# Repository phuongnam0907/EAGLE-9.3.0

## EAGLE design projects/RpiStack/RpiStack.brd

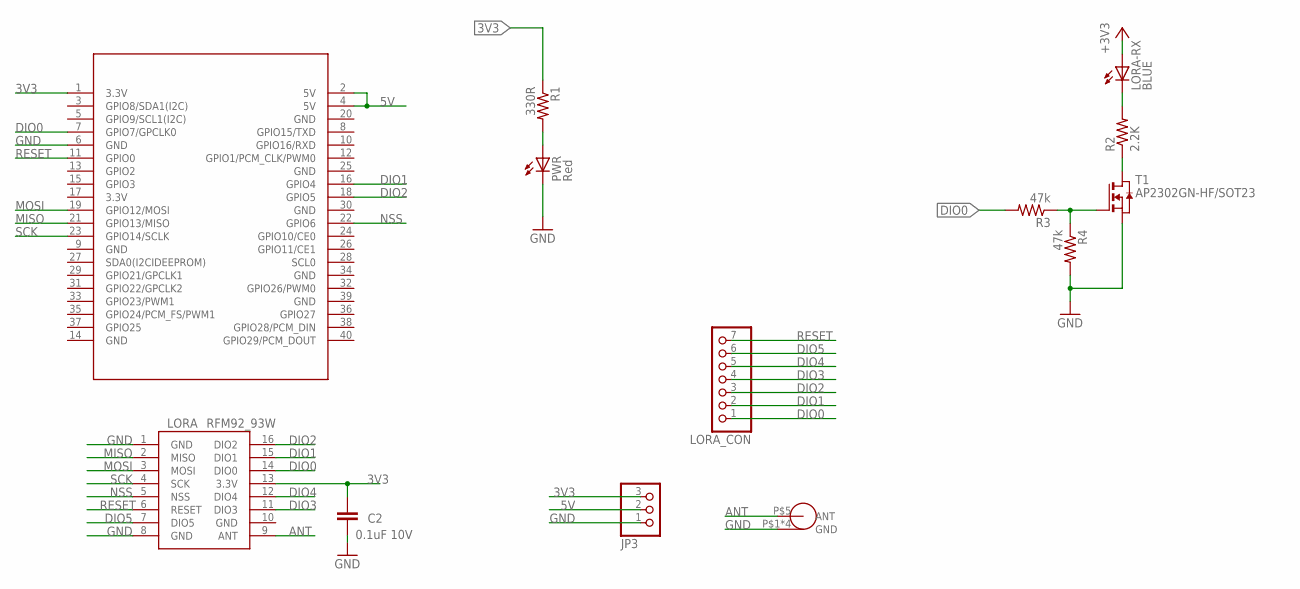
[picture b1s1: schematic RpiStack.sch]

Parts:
C2: 0.1uF 10V; C0402
JP3: PINHD-1X3; 1X03
LORA: RFM92_93W
LORA-RX: BLUE; CHIPLED_0603
LORA_ANT: SMA-KE
LORA_CON: PINHD-1X7; 1X07
PWR: Red; CHIPLED_0603
R1: 330R; R0402
R2: 2.2K; R0402
R3, R4: 47k; R0402
T1: AP2302GN-HF/SOT23; SOT-23
U$2: RPILORASHIELD

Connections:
3V3: C2.2, JP3.3, LORA.13 (3.3V), LORA-RX.A, R1.1, U$2.1 (3.3V)
5V: JP3.2, U$2.2 (5V), U$2.4 (5V)
/RESET: R2.1, T1.1 (D)
ANT: LORA.9 (ANT), LORA_ANT.P$5 (ANT)
DIO0: LORA.14 (DIO0), LORA_CON.1, R3.2, U$2.7 (GPIO7/GPCLK0)
DIO1: LORA.15 (DIO1), LORA_CON.2, U$2.16 (GPIO4)
DIO2: LORA.16 (DIO2), LORA_CON.3, U$2.18 (GPIO5)
DIO3: LORA.11 (DIO3), LORA_CON.4
DIO4: LORA.12 (DIO4), LORA_CON.5
DIO5: LORA.7 (DIO5), LORA_CON.6
GND: C2.1, JP3.1, LORA.1 (GND), LORA.8 (GND), LORA.10 (GND), LORA_ANT.P$1 (GND), LORA_ANT.P$2 (GND), LORA_ANT.P$3 (GND), LORA_ANT.P$4 (GND), PWR.C, R4.2, T1.2 (S), U$2.6 (GND)
MISO: LORA.2 (MISO), U$2.21 (GPIO13/MISO)
MOSI: LORA.3 (MOSI), U$2.19 (GPIO12/MOSI)
unnamed: R3.1, R4.1, T1.3 (G)
unnamed: PWR.A, R1.2
unnamed: LORA-RX.C, R2.2
NSS: LORA.5 (NSS), U$2.22 (GPIO6)
RESET: LORA.6 (RESET), LORA_CON.7, U$2.11 (GPIO0)
SCK: LORA.4 (SCK), U$2.23 (GPIO14/SCLK)

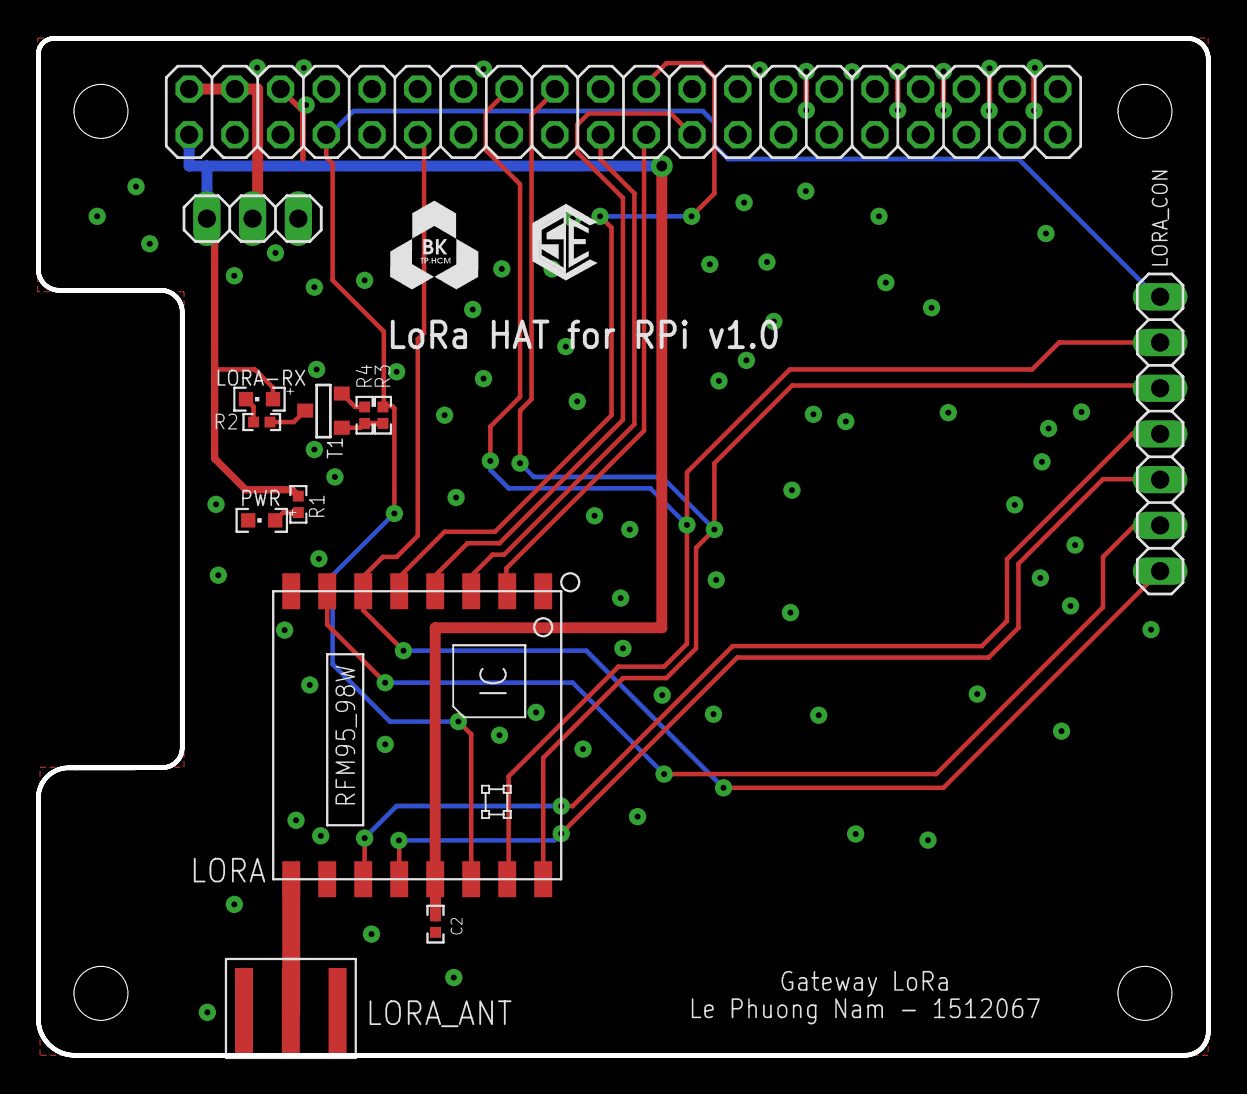
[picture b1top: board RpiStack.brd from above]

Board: 2 copper layers, 65.0 x 56.5 mm, 13 parts (0 on the bottom side), 19 nets.

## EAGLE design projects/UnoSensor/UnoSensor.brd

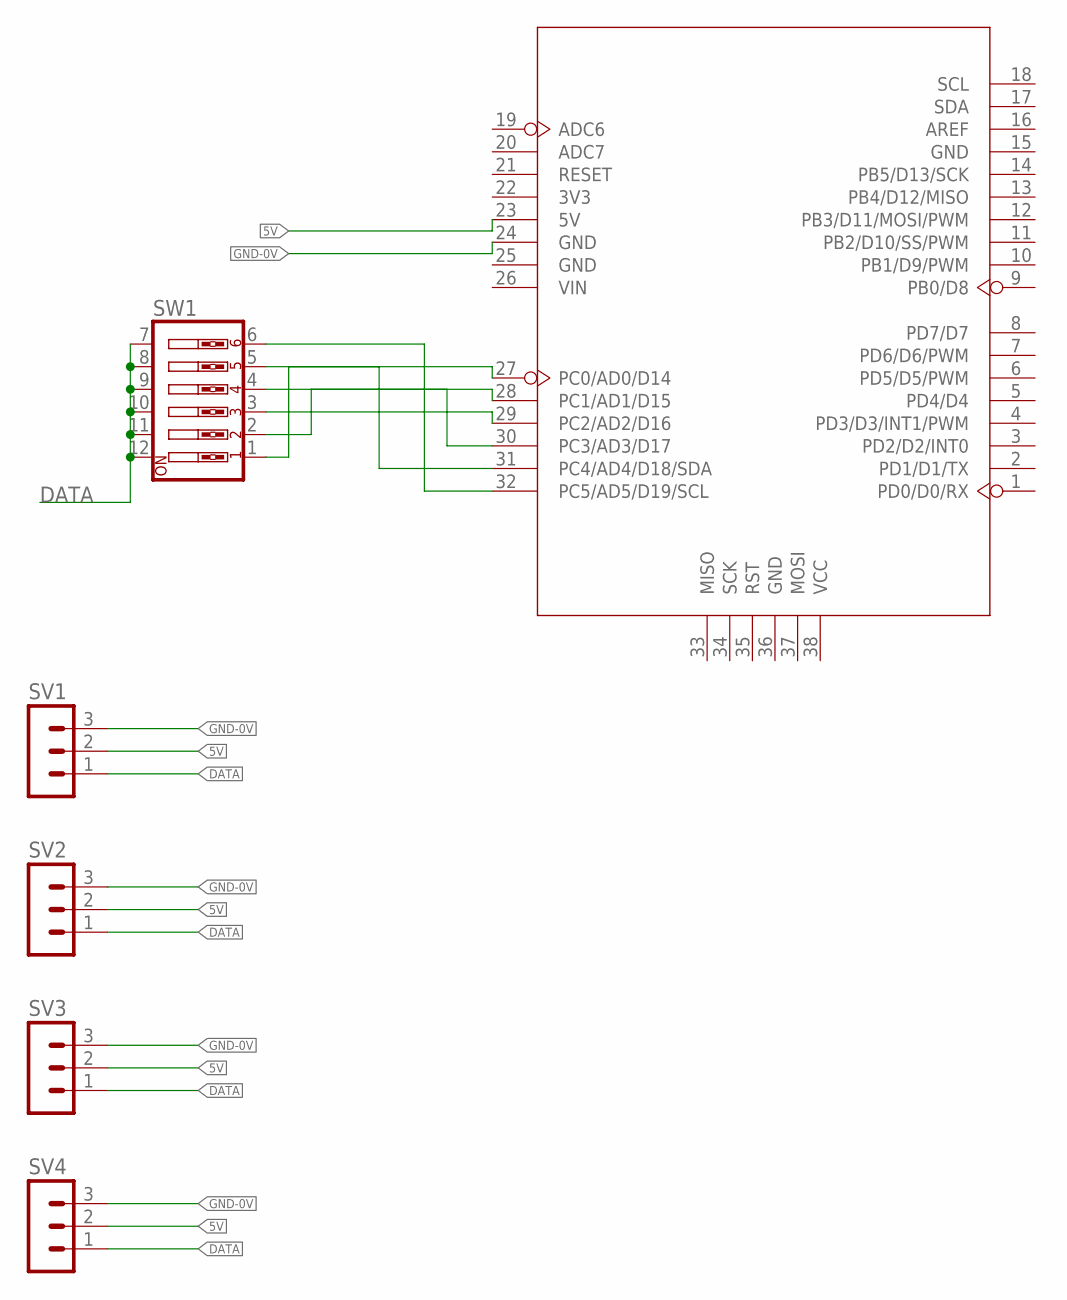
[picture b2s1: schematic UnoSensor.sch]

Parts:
SV1: 2; MA03-1
SV2, SV3, SV4: MA03-1
SW1: SW_DIP-6; EDG-06
U5: MOUDLE_ARDUINO-38P328P_NO_VIA; MOUDLE_ARDUINO-328P--

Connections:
5V: SV1.2, SV2.2, SV3.2, SV4.2, U5.23 (5V)
DATA: SV1.1, SV2.1, SV3.1, SV4.1, SW1.7, SW1.8, SW1.9, SW1.10, SW1.11, SW1.12
GND-0V: SV1.3, SV2.3, SV3.3, SV4.3, U5.24 (GND)
unnamed: SW1.1, U5.27 (PC0/AD0/D14)
unnamed: SW1.2, U5.28 (PC1/AD1/D15)
unnamed: SW1.3, U5.29 (PC2/AD2/D16)
unnamed: SW1.4, U5.30 (PC3/AD3/D17)
unnamed: SW1.5, U5.31 (PC4/AD4/D18/SDA)
unnamed: SW1.6, U5.32 (PC5/AD5/D19/SCL)

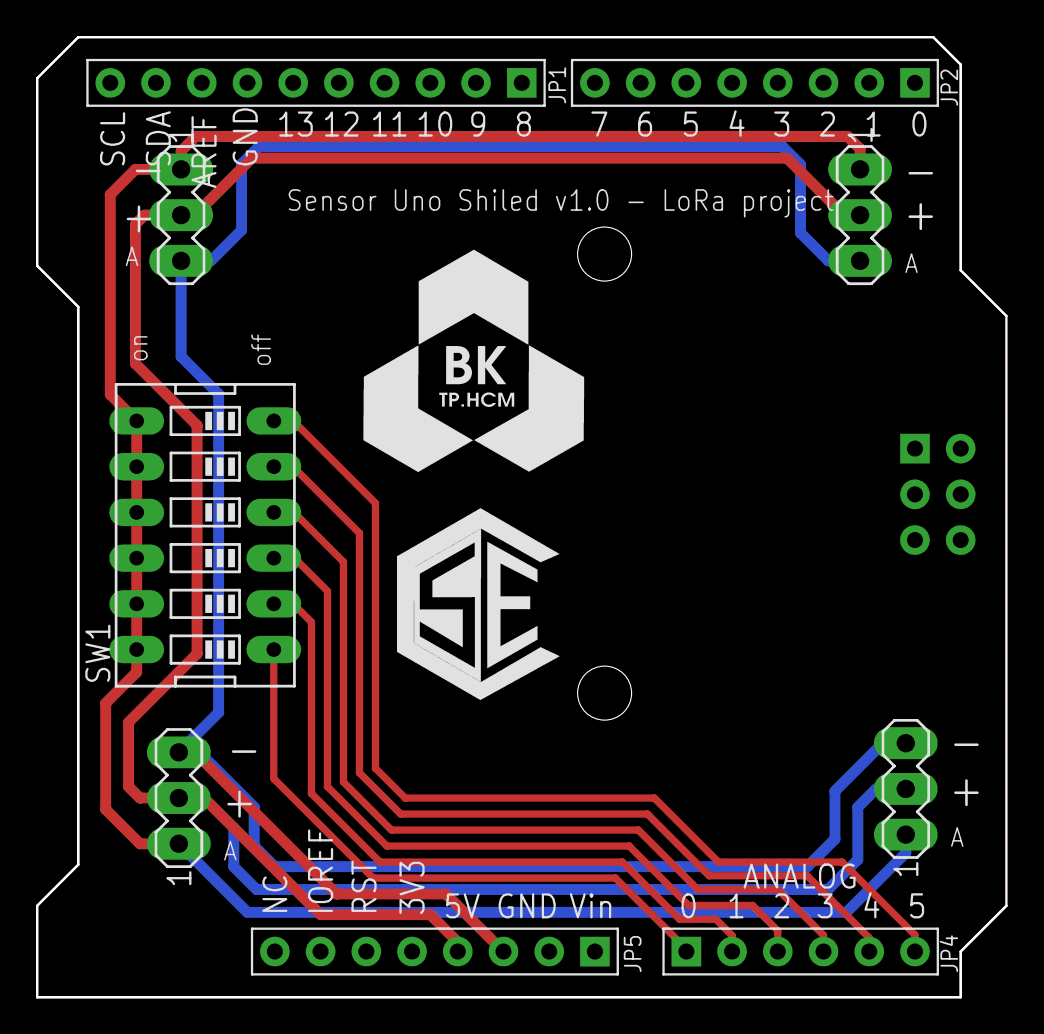
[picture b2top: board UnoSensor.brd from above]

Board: 2 copper layers, 53.8 x 53.3 mm, 6 parts (0 on the bottom side), 9 nets.

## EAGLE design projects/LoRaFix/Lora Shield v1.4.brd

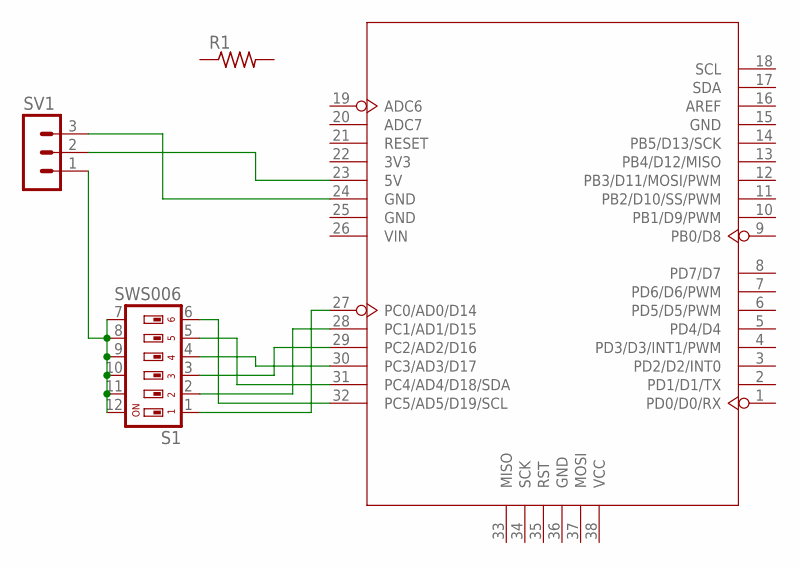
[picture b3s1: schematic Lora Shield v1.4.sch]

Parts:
R1: R-US_R0805; R0805
S1: SWS006; SMS-006
SV1: MA03-1
U5: MOUDLE_ARDUINO-38P328P_NO_VIA; MOUDLE_ARDUINO-328P--

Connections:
DATA: S1.7, S1.8, S1.9, S1.10, S1.11, S1.12, SV1.1
unnamed: S1.1, U5.27 (PC0/AD0/D14)
unnamed: S1.2, U5.28 (PC1/AD1/D15)
unnamed: S1.3, U5.29 (PC2/AD2/D16)
unnamed: S1.4, U5.30 (PC3/AD3/D17)
unnamed: S1.5, U5.31 (PC4/AD4/D18/SDA)
unnamed: S1.6, U5.32 (PC5/AD5/D19/SCL)
unnamed: SV1.3, U5.24 (GND)
unnamed: SV1.2, U5.23 (5V)

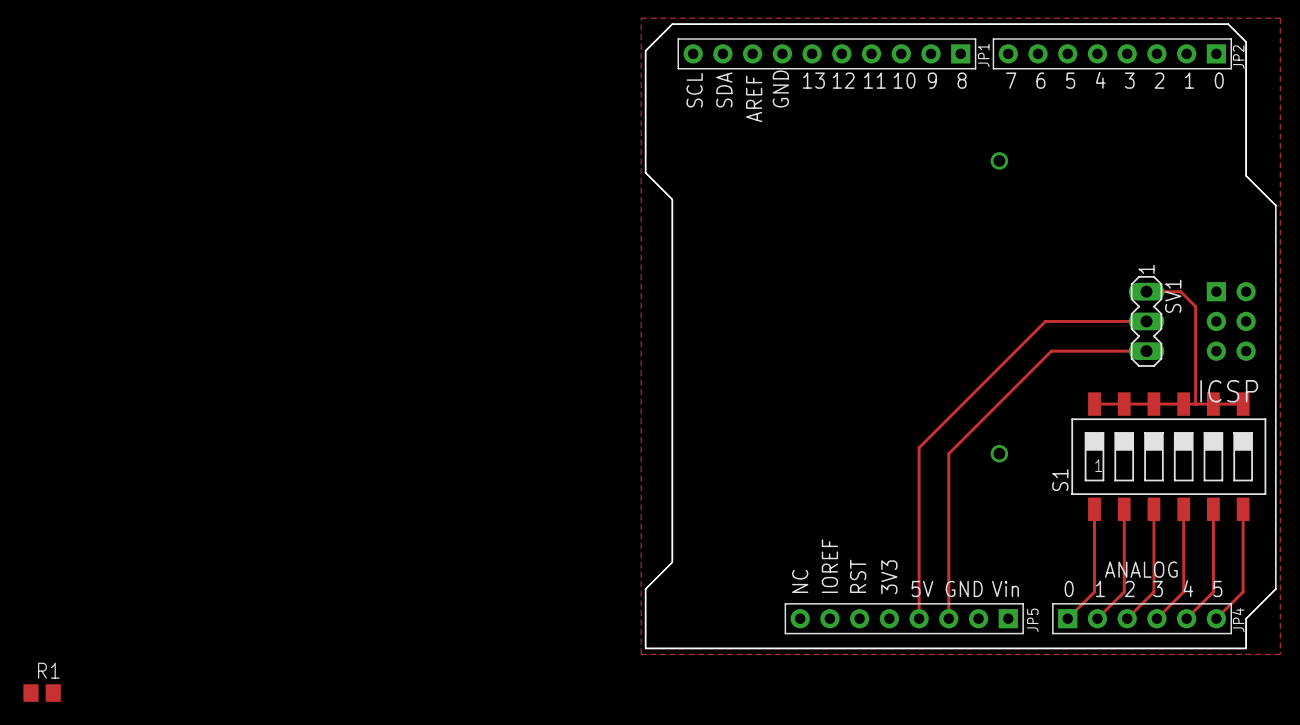
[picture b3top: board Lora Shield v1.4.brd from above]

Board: 2 copper layers, 53.8 x 53.3 mm, 4 parts (0 on the bottom side), 9 nets.

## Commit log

2019-03-14 init

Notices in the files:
parts and their libraries:
dragino: http://creativecommons.org/licenses/by-sa/3.0
dragino: Released under the CC Attribution Share-Alike 3.0 License
